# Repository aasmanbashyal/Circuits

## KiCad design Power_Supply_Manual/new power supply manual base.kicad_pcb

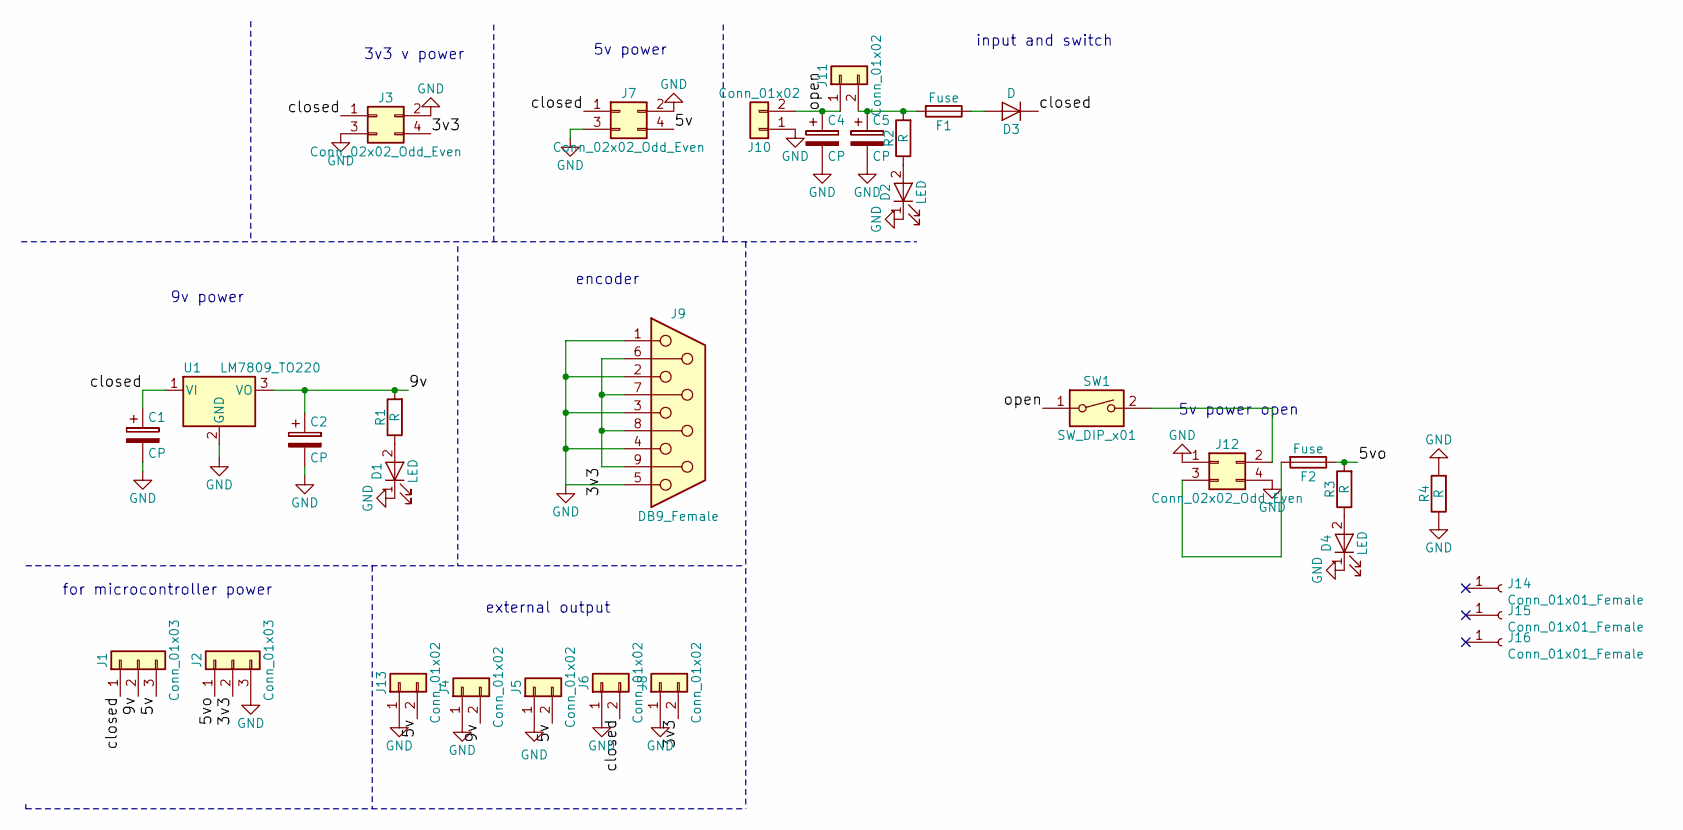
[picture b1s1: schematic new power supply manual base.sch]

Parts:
C1, C2: CP; Capacitor_10uF
C4, C5: CP; Capacitor_100uF
D1, D2, D4: LED; LED_D3.0mm
D3: D; Diode_Medium
F1, F2: Fuse; Fuse_Holder
J1, J2: Conn_01x03; Connector_Bornier_3
J3, J7, J12: Conn_02x02_Odd_Even; Buck_Regulator
J4, J5, J6, J8: Conn_01x02; Connector_Bornier_2
J9: DB9_Female; Connector_DB_9
J10, J11: Conn_01x02; Solar_Connector
J13: Conn_01x02; BARREL_JACK
J14, J15, J16: Conn_01x01_Female; 1pin
R1, R2, R3, R4: R; Resistor_small
SW1: SW_DIP_x01; DIP_Switch
U1: LM7809_TO220; TO-220_Vertical

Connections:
/3v3: J2.2, J3.4, J8.2, J9.6, J9.7, J9.8, J9.9
/5v: J1.3, J5.2, J7.4, J13.2
/5vo: F2.1, J2.1, R3.2
/9v: C2.1, J1.2, J4.2, R1.2, U1.3 (VO)
/closed: C1.1, D3.1 (K), J1.1, J3.1, J6.2, J7.1, U1.1 (VI)
/open: C4.1, J10.2, J11.1, SW1.1
GND: C1.2, C2.2, C4.2, C5.2, D1.1 (K), D2.1 (K), D4.1 (K), J2.3, J3.2, J3.3, J4.1, J5.1, J6.1, J7.2, J7.3, J8.1, J9.1, J9.2, J9.3, J9.4, J9.5, J10.1, J12.1, J12.4, J13.1, R4.1, R4.2, U1.2 (GND)
unnamed: C5.1, F1.2, J11.2, R2.2
unnamed: D1.2 (A), R1.1
unnamed: D2.2 (A), R2.1
unnamed: D3.2 (A), F1.1
unnamed: D4.2 (A), R3.1
unnamed: F2.2, J12.3
unnamed: J12.2, SW1.2

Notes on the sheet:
input and switch
for microcontroller power
external output
encoder
9v power
3v3 v power
5v power
5v power open

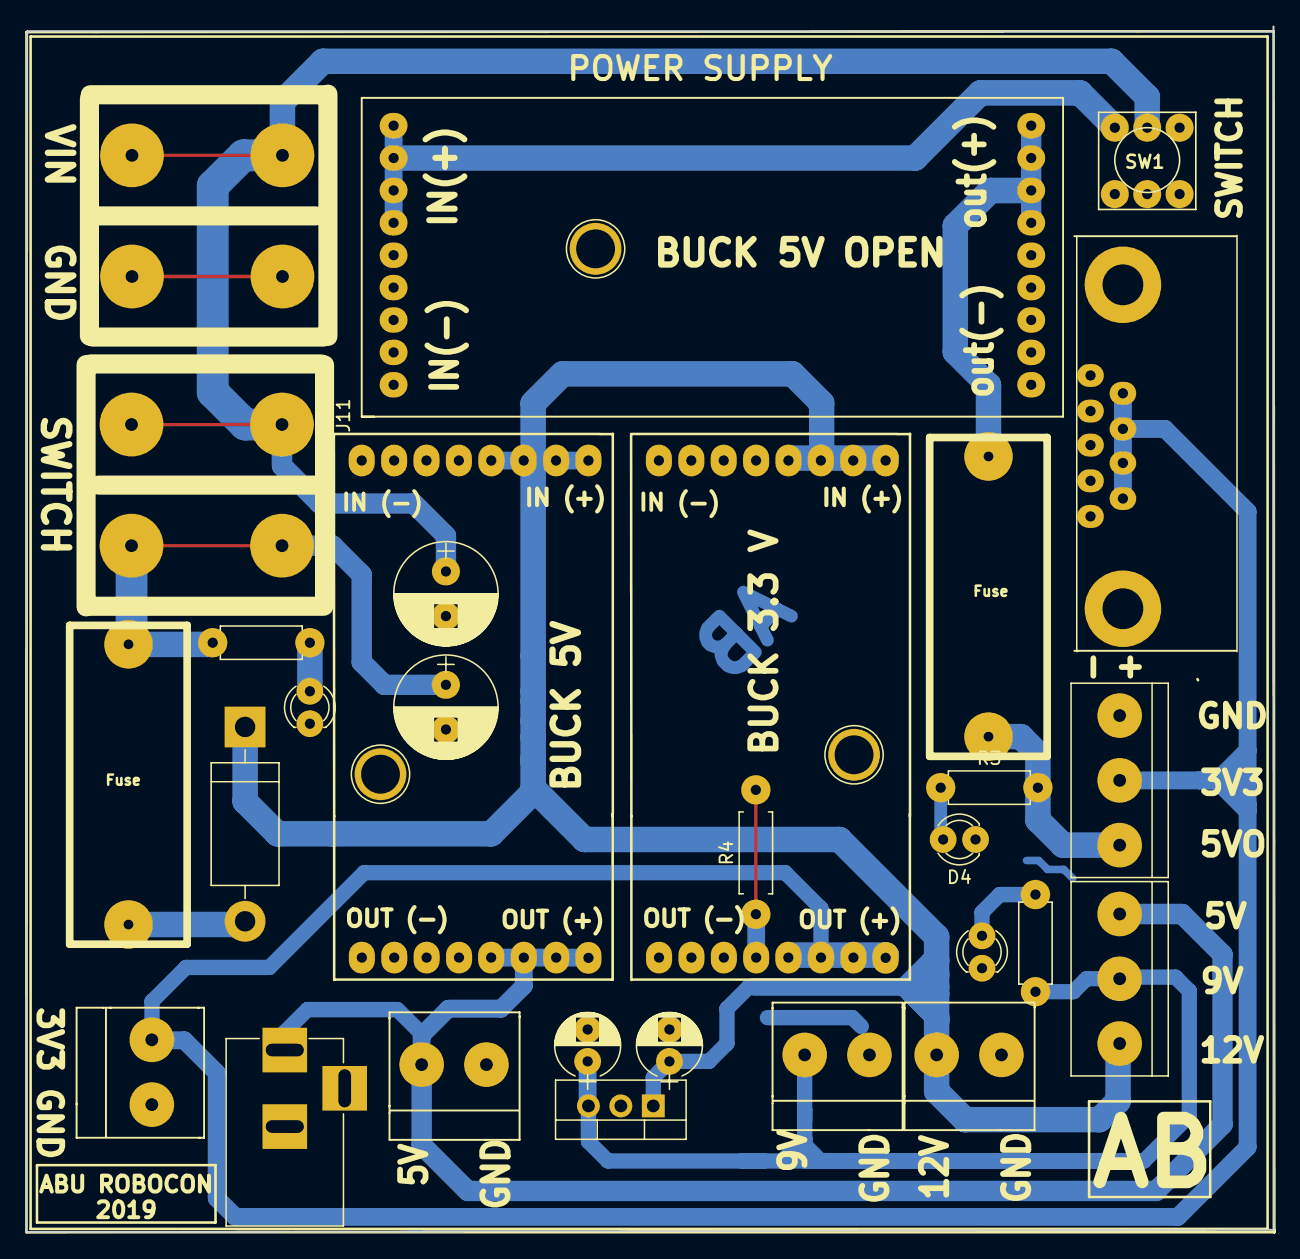
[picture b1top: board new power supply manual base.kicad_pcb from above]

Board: 2 copper layers, 97.8 x 94.6 mm, 32 parts (0 on the bottom side), 14 nets.

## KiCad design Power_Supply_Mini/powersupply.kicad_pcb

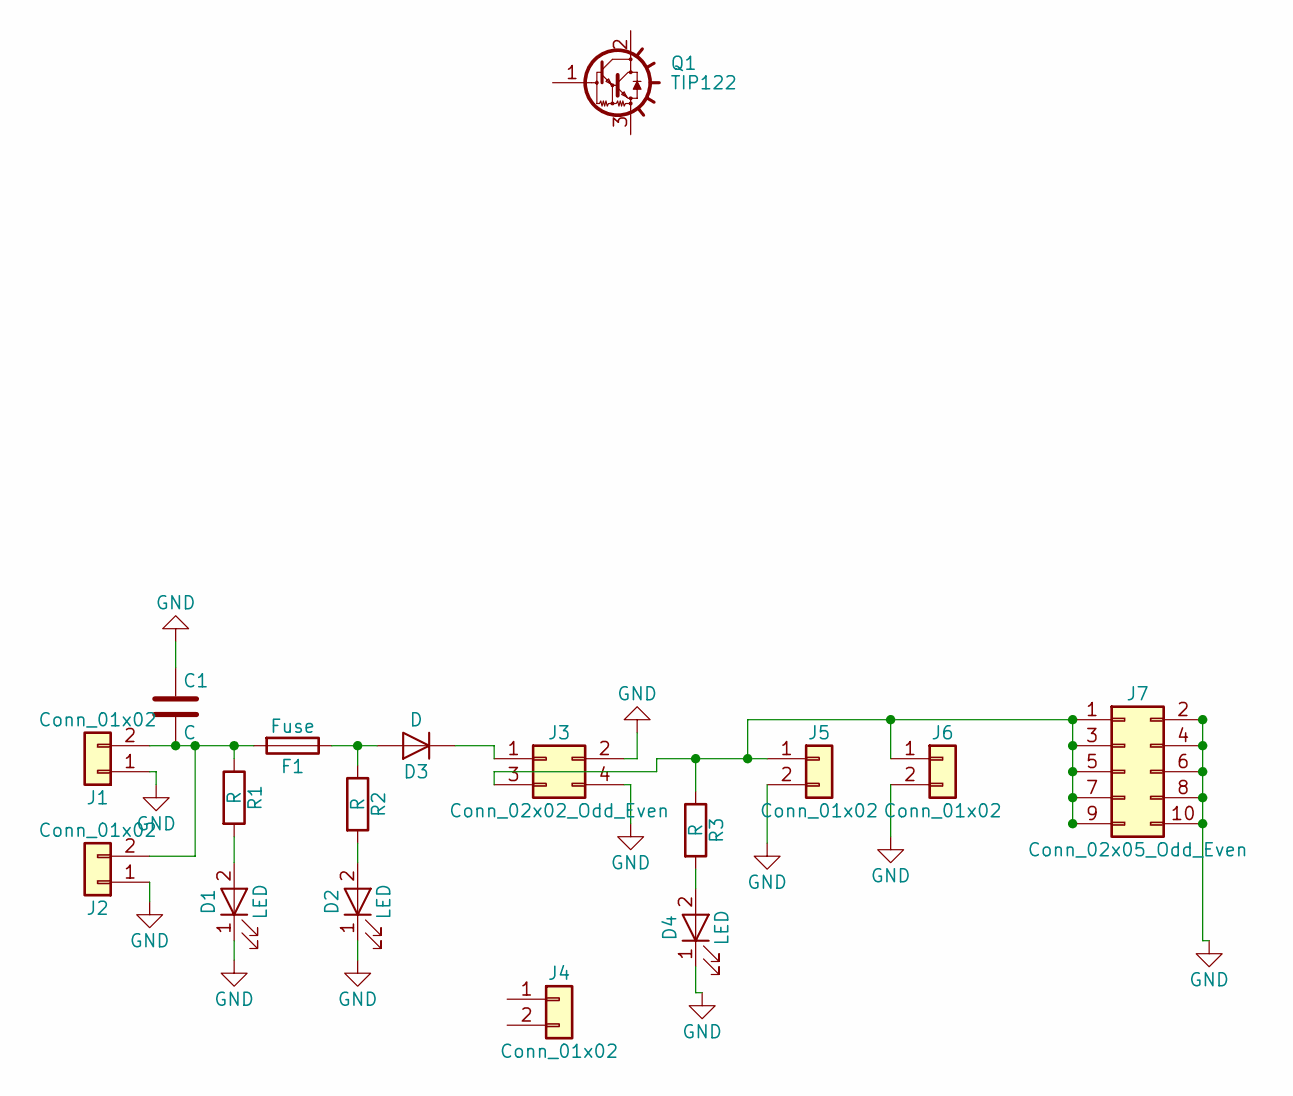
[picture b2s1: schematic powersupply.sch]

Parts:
C1: C; Capacitor_10uF
D1, D2, D4: LED; LED_D3.0mm
D3: D; Diode_Medium
F1: Fuse; Fuse_Holder
J1: Conn_01x02; Solar_Connector
J2, J4: Conn_01x02; BARREL_JACK
J3: Conn_02x02_Odd_Even; Buck_Regulator
J5: Conn_01x02; bornier2
J6: Conn_01x02; Pin_Header_Straight_1x02_Pitch2.54mm
J7: Conn_02x05_Odd_Even; Pin_Header_Straight_2x05_Pitch2.54mm
Q1: TIP122; TO-220_Vertical
R1, R2, R3: R; Resistor_small

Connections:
GND: C1.1, D1.1 (K), D2.1 (K), D4.1 (K), J1.1, J2.1, J3.2, J3.4, J5.2, J6.2, J7.2, J7.4, J7.6, J7.8, J7.10
unnamed: C1.2, F1.2, J1.2, J2.2, R1.1
unnamed: D1.2 (A), R1.2
unnamed: D2.2 (A), R2.2
unnamed: D3.1 (K), J3.1
unnamed: D3.2 (A), F1.1, R2.1
unnamed: D4.2 (A), R3.2
unnamed: J3.3, J5.1, J6.1, J7.1, J7.3, J7.5, J7.7, J7.9, R3.1

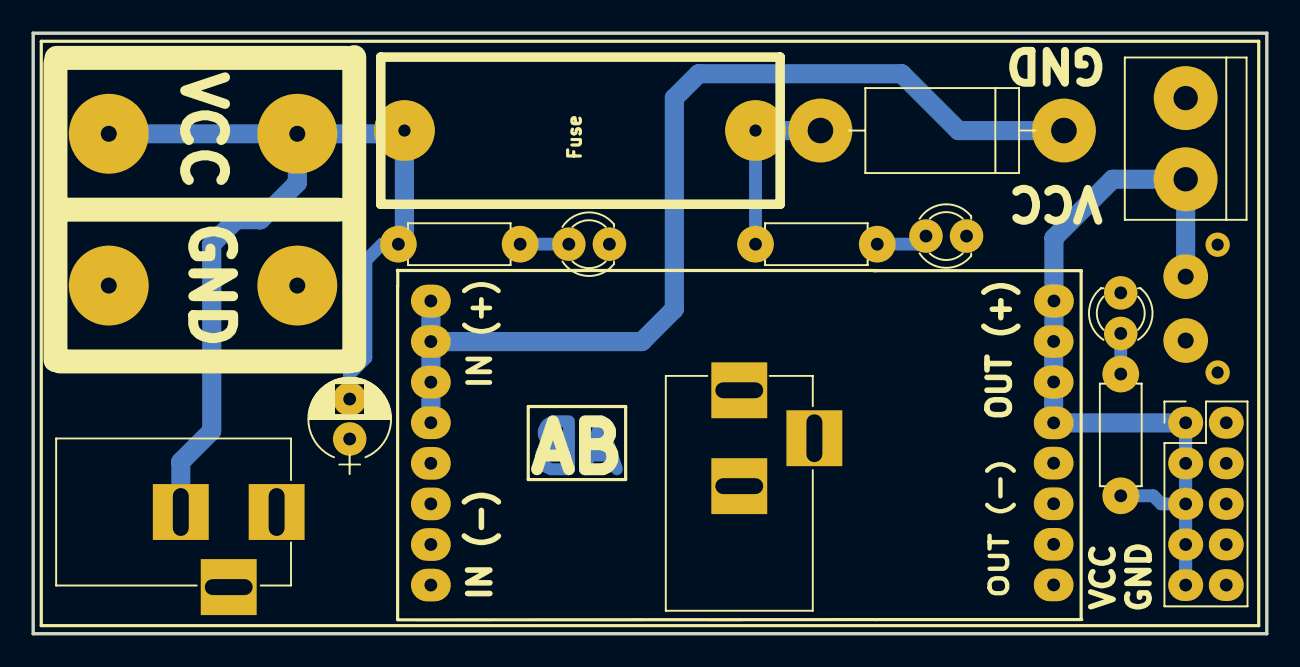
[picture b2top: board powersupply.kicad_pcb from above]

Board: 2 copper layers, 77.2 x 37.6 mm, 16 parts (0 on the bottom side), 8 nets.

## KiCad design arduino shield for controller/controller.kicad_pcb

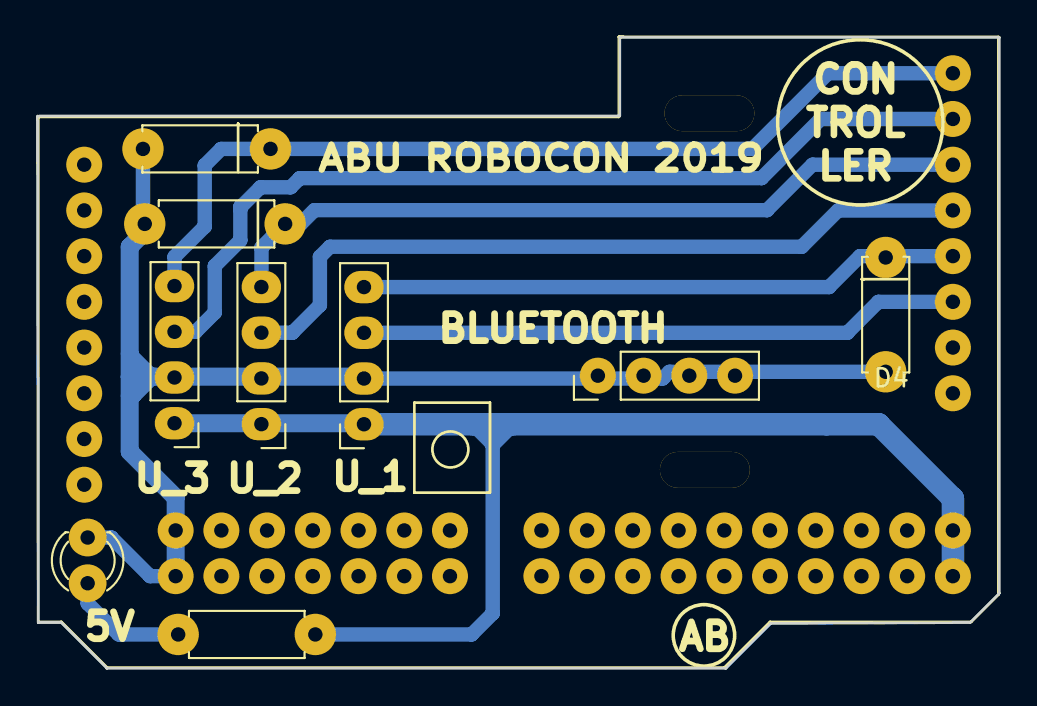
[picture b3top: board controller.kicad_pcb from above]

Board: 2 copper layers, 53.4 x 35.1 mm, 10 parts (0 on the bottom side), 9 nets.

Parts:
D1: LED; LED_D3.0mm
D2, D3, D4: D_Zener; Resistor_small
J1: Conn_01x04; bluetooth
J2, J3, J4: Conn_01x04; Pin_Header_Straight_1x04_Pitch2.54mm
R1: R; Resistor_small
U1: Arduino_Mega2560_Shield

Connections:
+5V: J1.1, J2.1, J3.1, R1.2, U1.5V1
/RX_01: J1.3, U1.19
/RX_02: J2.3, U1.17
/RX_03: J3.3, U1.15
/TX_01: D4.1, J1.4, U1.18
/TX_02: D3.1, J2.4, U1.16
/TX_03: D2.1, J3.4, U1.14
GND: D1.1, D2.2, D3.2, D4.2, J1.2, J2.2, J3.2, J4.1, J4.2, J4.3, J4.4, U1.GND1, U1.GND2
unnamed: D1.2, R1.1

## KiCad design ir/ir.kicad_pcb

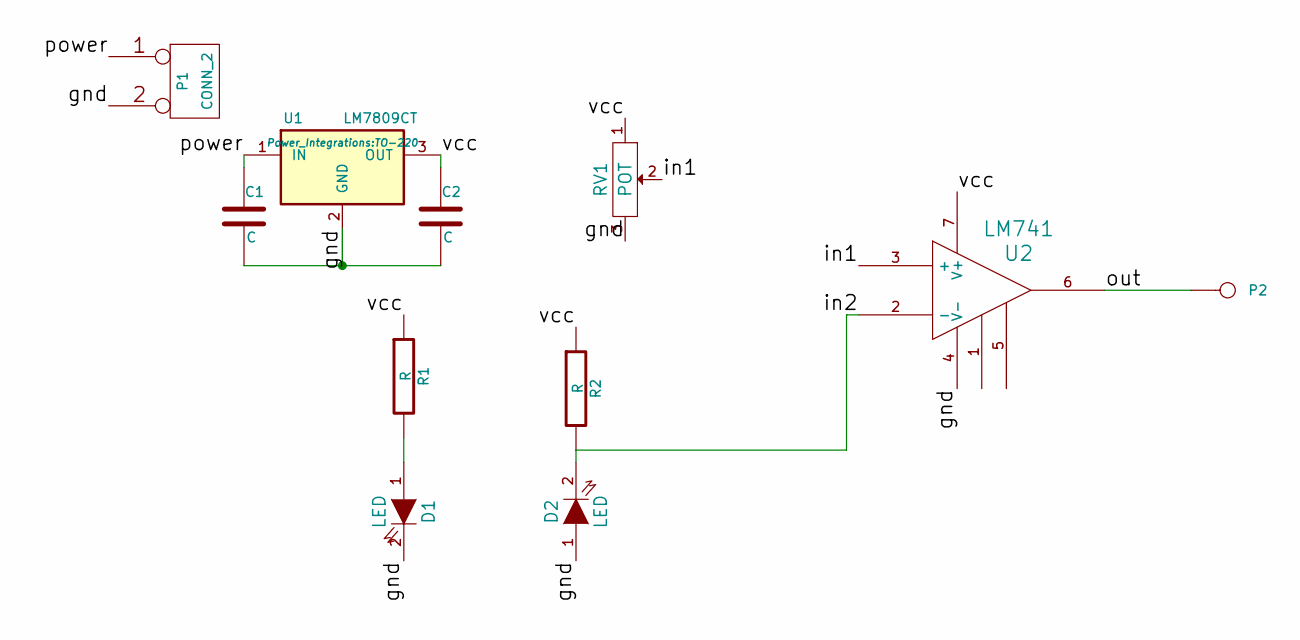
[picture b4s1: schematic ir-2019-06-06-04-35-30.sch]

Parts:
C1: C; CP_Radial_D6.3mm_P2.50mm
C2: C; CP_Radial_D5.0mm_P2.50mm
D1, D2: LED; LED_D3.0mm
P1: CONN_2; Pin_Header_Straight_1x02_Pitch2.54mm
P2: CONN_1; Pin_Header_Straight_1x01_Pitch2.54mm
R1, R2: R; R_Axial_DIN0207_L6.3mm_D2.5mm_P7.62mm_Horizontal
RV1: POT; Potentiometer_Trimmer_ACP_CA9VSMD_Horizontal_Px9.2mm_Py5.0m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
U1: LM7809CT; TO-220
U2: LM741; DIP-8_W7.62mm_Socket

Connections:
/gnd: C1.2, C2.2, D1.2 (K), D2.1 (A), P1.2 (PM), RV1.3, U1.2 (GND), U2.4 (V-)
/in1: RV1.2, U2.3 (+)
/in2: D2.2 (K), R2.2, U2.2 (-)
/out: P2.1, U2.6
/power: C1.1, P1.1, U1.1 (IN)
/vcc: C2.1, R1.1, R2.1, RV1.1, U1.3 (OUT), U2.7 (V+)
unnamed: D1.1 (A), R1.2

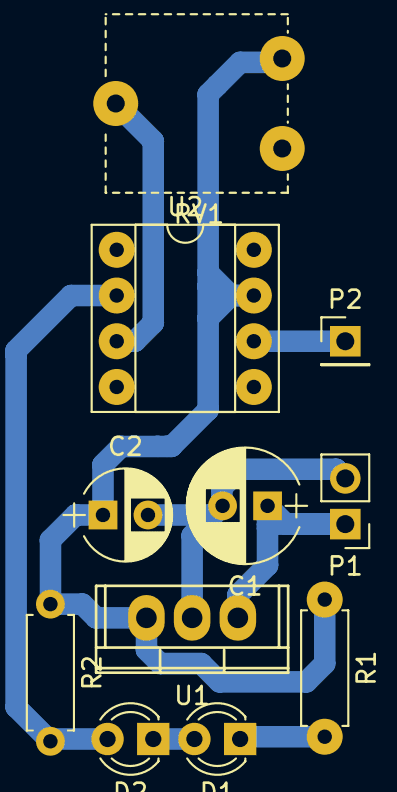
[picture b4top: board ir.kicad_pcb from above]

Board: 2 copper layers, 11 parts (0 on the bottom side), 7 nets.

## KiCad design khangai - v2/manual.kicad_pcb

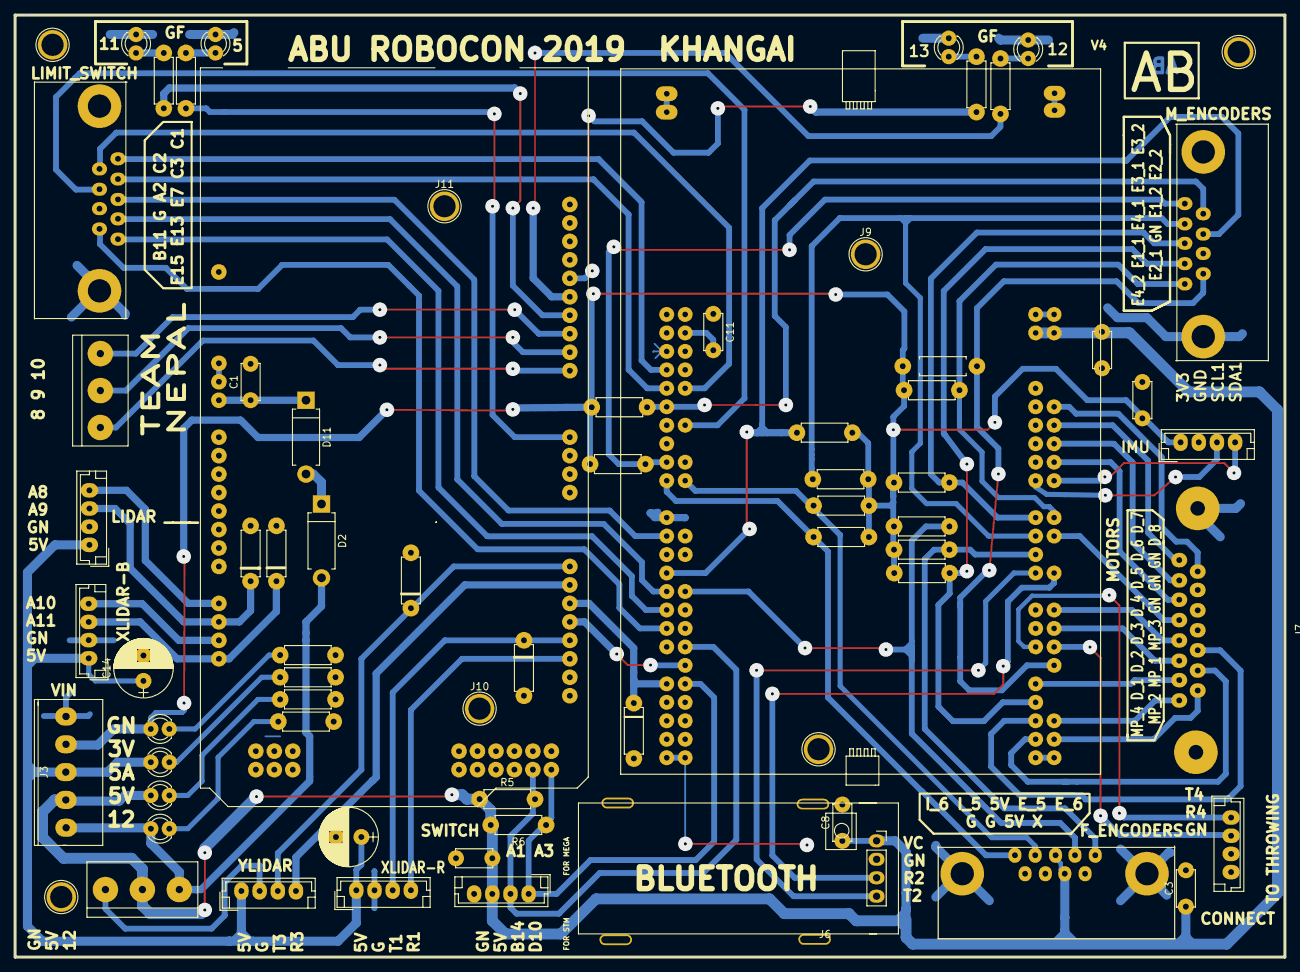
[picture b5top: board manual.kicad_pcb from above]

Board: 2 copper layers, 174.6 x 129.5 mm, 70 parts (0 on the bottom side), 73 nets.

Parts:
C1, C3, C4, C5, C7, C8, C11: C; Capacitor_Disc_Medium
C13, C14: CP; Capacitor_100uF
D1, D7, D8, D9, D10: D_Zener; Resistor_small
D2, D11: D; Diode_Small
D3, D4, D5, D6, D12, D13, D14, D15: LED; LED_D3.0mm
J1, J2, J4, J13, J23, J24: Conn_01x04; jst_4
J3: Conn_01x05; JST_5_BIG
J5, J16, J17: DB9_Female; Connector_DB_9
J6: Conn_01x04; bluetooth
J7: DB15_Female; Connector_DB15
J8, J25: Conn_01x03; Connector_Bornier_3
J9, J10, J11, J19, J20, J21, J22: Conn_01x01_Female; 1pin
J18: Conn_01x04; JST_EH_B04B-EH-A_04x2.50mm_Straight
R1, R2, R3, R4, R5, R6, R10, R11, R12, R13, R18, R19, R20, R21, R22, R23, R24, R25, R26, R27, R28, R29: R; Resistor_small
U1: STM32F407_Discovery
U2: Arduino_Mega2560_Shield

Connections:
+3V3: C4.1, D6.2, J3.4, J4.1, R18.1, R19.1, R20.1, R21.1, R22.1, R23.1, R24.1, R25.1, R26.1, R27.1, R28.1, R29.1
+5V: C3.1, C5.1, C7.1, C8.1, D4.2, J2.3, J3.2, J6.1, J8.2, J17.3, J17.7, R5.1, R6.2, U1.53, U1.54
+5VA: C13.1, C14.1, D5.2, J3.3, J13.1, J18.1, J23.1, J24.1
+12V: D2.2, D3.2, J3.1, J8.1
/12C1_SCL: J4.3, U1.69
/12C1_SDA: J4.4, U1.70
/D_1: J7.7, U1.91
/D_2: J7.6, U1.86
/D_3: J7.5, U1.84
/D_4: J7.4, U1.76
/D_5: J7.3, U1.68
/D_6: J7.2, U1.66
/D_7: J7.1, U1.64
/D_8: J7.9, U1.62
/EM_3_CH1: J16.2, R22.2, U1.75
/EM_3_CH2: J16.1, R23.2, U1.17
/EN_1_CH1: J16.4, R18.2, U1.93
/EN_1_CH2: J16.7, R19.2, U1.29
/EN_2_CH1: J16.9, R20.2, U1.90
/EN_2_CH2: J16.6, R21.2, U1.11
/EN_4_CH1: J16.3, R24.2, U1.73
/EN_4_CH2: J16.5, R25.2, U1.74
/EN_5: J17.2, R26.2, U1.32
/EN_6: J17.1, R28.2, U1.77
/G_01: J5.9, U1.10
/G_02: J5.8, U1.14
/G_03: J5.5, U1.7
/G_04: J5.4, U1.9
/G_08: J5.3, U1.25
/G_09: J5.2, U1.31
/G_10: J5.1, U1.33
/G_11: J5.6, U1.35
/IN_1: J2.1, R5.2, U1.38, U2.25
/IN_2: J2.2, R6.1, U1.42, U2.23
/IN_5: J17.4, R27.2, U1.20
/IN_6: J17.5, R29.2, U1.19
/M_PWM_1: J7.14, U1.97
/M_PWM_2: J7.15, U1.98
/M_PWM_3: J7.13, U1.95
/M_PWM_4: J7.8, U1.96
/UART2_RX: J6.3, U1.80
/UART2_TX: J6.4, U1.79
/USART3_RX: D1.1, U1.41, U2.16
/USART3_TX: U1.40, U2.17
/USART4_RX: J1.2, U1.88
/USART4_TX: J1.1, U1.87
/mega/RX_1: J13.4, U2.19
/mega/RX_3: J18.4, U2.15
/mega/S1_RX: J24.4, U2.A8
/mega/S1_TX: D8.1, J24.3, U2.A9
/mega/S2_RX: J23.4, U2.A10
/mega/S2_TX: D9.1, J23.3, U2.A11
/mega/TX_1: D7.1, J13.3, U2.18
/mega/TX_3: D10.1, J18.3, U2.14
/mega/d8: J25.3, U2.8
/mega/d9: J25.2, U2.9
/mega/d10: J25.1, U2.10
GND: C1.2, C3.2, C4.2, C5.2, C7.2, C8.2, C11.1, C13.2, C14.2, D1.2, D7.2, D8.2, D9.2, D10.2, D12.1, D13.1, D14.1, D15.1, J1.3, J1.4, J2.4, J3.5, J4.2, J5.7, J6.2, J7.10, J7.11, J7.12, J8.3, J13.2, J16.8, J17.6, J17.8, J17.9, J18.2, J23.2, J24.2, R10.1, R11.1, R12.1, R13.1, U1.1, U1.2, U1.5, U1.23, U1.49, U1.50, U1.51, U1.52, U1.99, U1.100, U2.GND1, U2.GND2
unnamed: C1.1, D11.1, U2.VIN
unnamed: C11.2, U1.4
unnamed: D3.1, R10.2
unnamed: D4.1, R11.2
unnamed: D5.1, R12.2
unnamed: D6.1, R13.2
unnamed: D2.1, D11.2
unnamed: D12.2, R1.1
unnamed: D13.2, R2.1
unnamed: D14.2, R4.1
unnamed: D15.2, R3.1
unnamed: R1.2, U2.13
unnamed: R2.2, U2.12
unnamed: R3.2, U2.11
unnamed: R4.2, U2.5

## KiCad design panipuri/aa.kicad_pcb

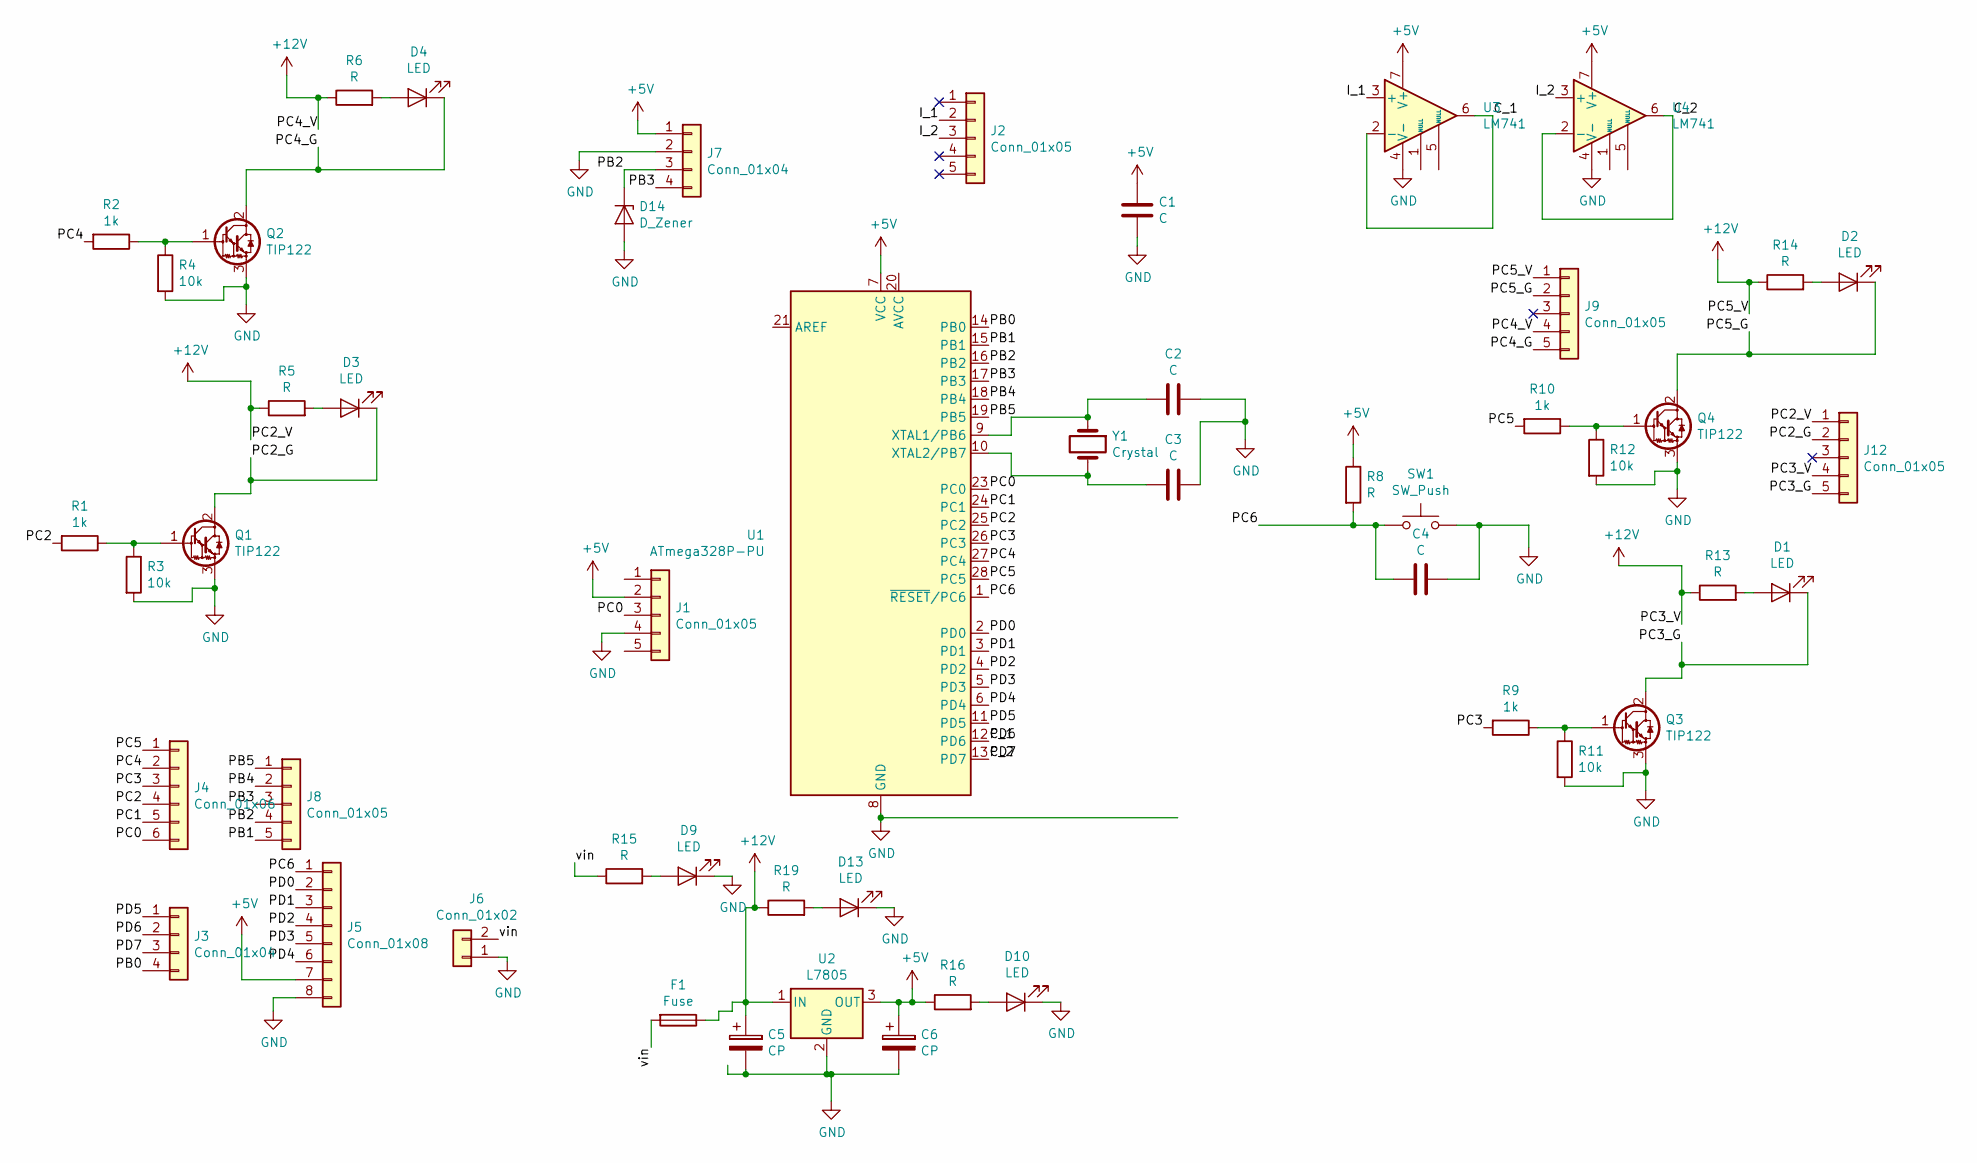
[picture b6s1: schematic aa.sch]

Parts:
C1, C2, C3, C4: C; Capacitor_Disc_Small
C5, C6: CP; Capacitor_10uF
D1, D2, D3, D4, D9, D10, D13: LED; LED_D3.0mm
D14: D_Zener; Resistor_small
F1: Fuse; Fuse_Holder
J1, J2, J9, J12: Conn_01x05; new_5_jst_bournier
J3, J7: Conn_01x04; Pin_Header_Straight_1x04_Pitch2.54mm
J4: Conn_01x06; Pin_Header_Straight_1x06_Pitch2.54mm
J5: Conn_01x08; Pin_Header_Straight_1x08_Pitch2.54mm
J6: Conn_01x02; Solar_Connector
J8: Conn_01x05; Pin_Header_Straight_1x05_Pitch2.54mm
Q1, Q2, Q3, Q4: TIP122; Voltage_Regulators
R1, R2, R9, R10: 1k; Resistor_small
R3, R4, R11, R12: 10k; Resistor_small
R5, R6, R8, R13, R14, R15, R16, R19: R; Resistor_small
SW1: SW_Push; Push_Button
U1: ATmega328P-PU; DIP-28
U2: L7805; Voltage_Regulators
U3, U4: LM741; DIP-8_W7.62mm
Y1: Crystal

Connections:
+5V: C1.1, C6.1, J1.2, J5.7, J7.1, R8.1, R16.1, U1.7 (VCC), U2.3 (OUT), U3.7 (V+), U4.7 (V+)
+12V: C5.1, F1.1, J9.1, J9.4, J12.1, J12.4, R5.1, R6.1, R13.1, R14.1, R19.1, U2.1 (IN)
/C_1: J3.2, U1.12 (PD6), U3.2 (-), U3.6
/C_2: J3.3, U1.13 (PD7), U4.2 (-), U4.6
/I_1: J2.2, U3.3 (+)
/I_2: J2.3, U4.3 (+)
/PB0: J3.4, U1.14 (PB0)
/PB1: J8.5, U1.15 (PB1)
/PB2: D14.1 (K), J7.3, J8.4, U1.16 (PB2)
/PB3: J7.4, J8.3, U1.17 (PB3)
/PB4: J8.2, U1.18 (PB4)
/PB5: J8.1, U1.19 (PB5)
/PC0: J1.3, J4.6, U1.23 (PC0)
/PC1: J4.5, U1.24 (PC1)
/PC2: J4.4, R1.2, U1.25 (PC2)
/PC2_G: D3.1 (K), J12.2, Q1.2 (C)
/PC3: J4.3, R9.2, U1.26 (PC3)
/PC3_G: D1.1 (K), J12.5, Q3.2 (C)
/PC4: J4.2, R2.2, U1.27 (PC4)
/PC4_G: D4.1 (K), J9.5, Q2.2 (C)
/PC5: J4.1, R10.2, U1.28 (PC5)
/PC5_G: D2.1 (K), J9.2, Q4.2 (C)
/PC6: C4.2, J5.1, R8.2, SW1.1, U1.1 (~RESET~/PC6)
/PD0: J5.2, U1.2 (PD0)
/PD1: J5.3, U1.3 (PD1)
/PD2: J5.4, U1.4 (PD2)
/PD3: J5.5, U1.5 (PD3)
/PD4: J5.6, U1.6 (PD4)
/PD5: J3.1, U1.11 (PD5)
/vin: F1.2, J6.2, R15.1
GND: C1.2, C2.1, C3.1, C4.1, C5.2, C6.2, D9.1 (K), D10.1 (K), D13.1 (K), D14.2 (A), J1.4, J5.8, J6.1, J7.2, Q1.3 (E), Q2.3 (E), Q3.3 (E), Q4.3 (E), R3.2, R4.2, R11.2, R12.2, SW1.2, U1.8 (GND), U1.22 (GND), U2.2 (GND), U3.4 (V-), U4.4 (V-)
unnamed: C2.2, U1.9 (XTAL1/PB6), Y1.1
unnamed: C3.2, U1.10 (XTAL2/PB7), Y1.2
unnamed: D1.2 (A), R13.2
unnamed: D2.2 (A), R14.2
unnamed: D3.2 (A), R5.2
unnamed: D4.2 (A), R6.2
unnamed: D9.2 (A), R15.2
unnamed: D10.2 (A), R16.2
unnamed: D13.2 (A), R19.2
unnamed: Q1.1 (B), R1.1, R3.1
unnamed: Q2.1 (B), R2.1, R4.1
unnamed: Q3.1 (B), R9.1, R11.1
unnamed: Q4.1 (B), R10.1, R12.1

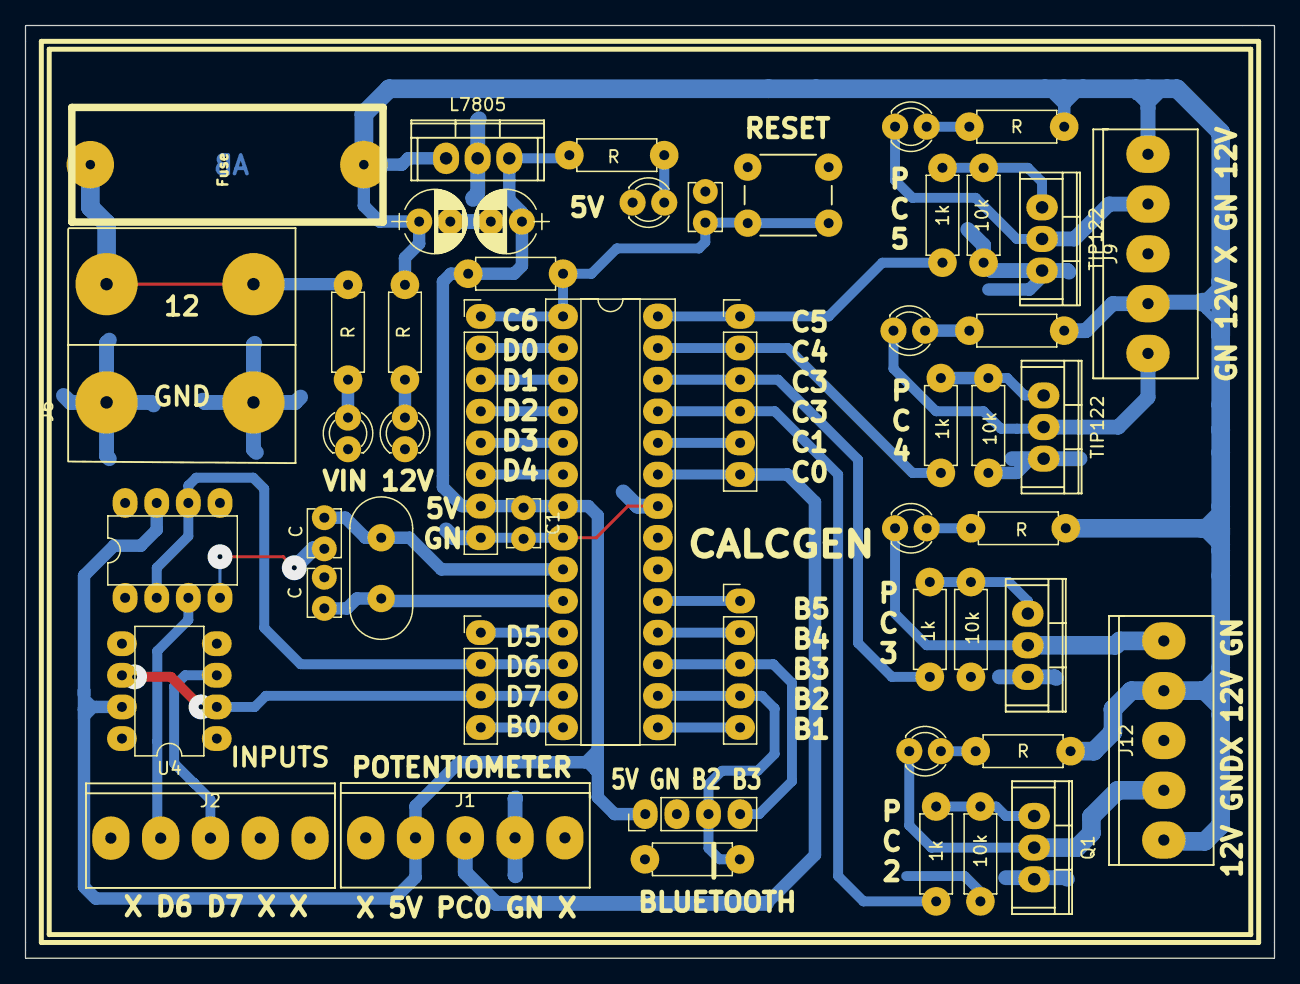
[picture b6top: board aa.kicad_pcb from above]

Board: 2 copper layers, 100.3 x 74.9 mm, 51 parts (0 on the bottom side), 44 nets.
